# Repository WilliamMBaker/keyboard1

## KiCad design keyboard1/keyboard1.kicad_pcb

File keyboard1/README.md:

This is a Kicad Template project (that also happens to be a dev-board) for the STM32F072CBT6.

***THIS PROJECT IS NOT PIN-COMPATIBLE OR PHYSICALLY COMPATIBLE WITH PROJECTS THAT USE A BLACKPILL OR ANY OTHER STM DEV-BOARD***

**THIS IS NOT A BLACKPILL OR BLUEPILL REPLACEMENT**

****See this video for turning this template into a BlackPill-compatible dev board:**** https://youtu.be/LvX-Us9VZM0

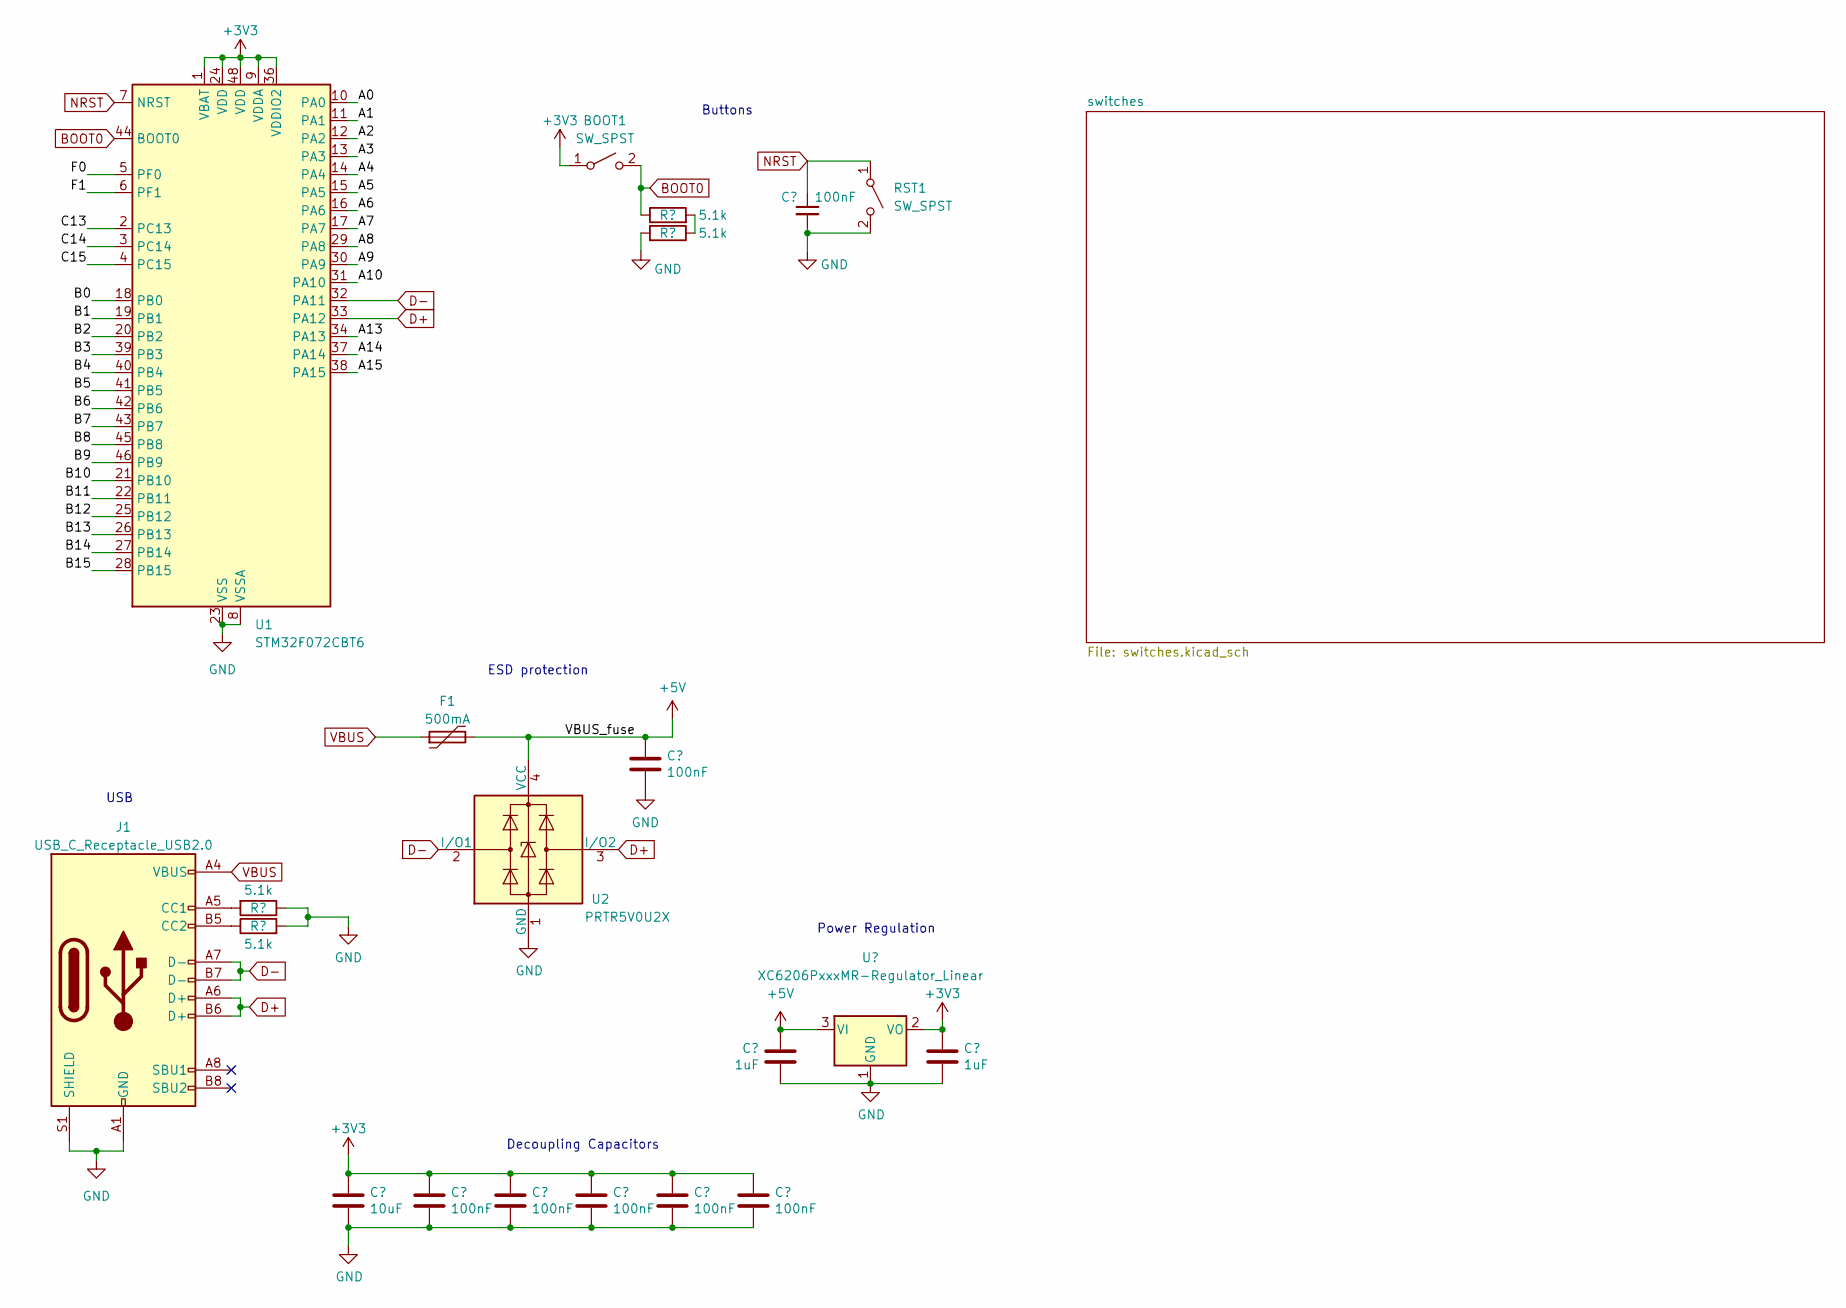
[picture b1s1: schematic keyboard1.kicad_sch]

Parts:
BOOT1: SW_SPST; SW_SPST_TL3342
C1, C3, C4, C5, C6, C7, C8: 100nF; C_0402_1005Metric; LCSC C307331
C2: 10uF; C_0603_1608Metric; LCSC C307331
C9, C10: 1uF; C_0402_1005Metric; LCSC C307331
F1: 500mA; Fuse_1206_3216Metric; LCSC C135341
J1: USB_C_Receptacle_USB2.0; USB_C_Receptacle_HRO_TYPE-C-31-M-12; JlcRotOffset 180
R1, R2, R3, R4: 5.1k; R_0402_1005Metric
RST1: SW_SPST; SW_SPST_TL3342
U1: STM32F072CBT6; LQFP-48_7x7mm_P0.5mm; JlcRotOffset 90
U2: PRTR5V0U2X; SOT-143; LCSC C2827688
U3: XC6206PxxxMR-Regulator_Linear; SOT-23; LCSC C5446

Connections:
+3V3: BOOT1.1 (A), C2.1, C3.1, C4.1, C5.1, C6.1, C7.1, C10.1, U1.1 (VBAT), U1.9 (VDDA), U1.24 (VDD), U1.36 (VDDIO2), U1.48 (VDD), U3.2 (VO)
+5V: C8.1, C9.1, F1.2, U2.4 (VCC), U3.3 (VI)
/A0: U1.10 (PA0)
/A1: U1.11 (PA1)
/A2: U1.12 (PA2)
/A3: U1.13 (PA3)
/A4: U1.14 (PA4)
/A5: U1.15 (PA5)
/A6: U1.16 (PA6)
/A7: U1.17 (PA7)
/A8: U1.29 (PA8)
/A9: U1.30 (PA9)
/A10: U1.31 (PA10)
/A13: U1.34 (PA13)
/A14: U1.37 (PA14)
/A15: U1.38 (PA15)
/B0: U1.18 (PB0)
/B1: U1.19 (PB1)
/B2: U1.20 (PB2)
/B3: U1.39 (PB3)
/B4: U1.40 (PB4)
/B5: U1.41 (PB5)
/B6: U1.42 (PB6)
/B7: U1.43 (PB7)
/B8: U1.45 (PB8)
/B9: U1.46 (PB9)
/B10: U1.21 (PB10)
/B11: U1.22 (PB11)
/B12: U1.25 (PB12)
/B13: U1.26 (PB13)
/B14: U1.27 (PB14)
/B15: U1.28 (PB15)
/C13: U1.2 (PC13)
/C14: U1.3 (PC14)
/C15: U1.4 (PC15)
/F0: U1.5 (PF0)
/F1: U1.6 (PF1)
BOOT0: BOOT1.2 (B), R3.1, U1.44 (BOOT0)
D+: J1.A6 (D+), J1.B6 (D+), U1.33 (PA12), U2.3 (I/O2)
D-: J1.A7 (D-), J1.B7 (D-), U1.32 (PA11), U2.2 (I/O1)
GND: C1.2, C2.2, C3.2, C4.2, C5.2, C6.2, C7.2, C8.2, C9.2, C10.2, J1.A1 (GND), J1.A12 (GND), J1.B1 (GND), J1.B12 (GND), J1.S1 (SHIELD), R1.1, R2.2, R4.2, RST1.2 (B), U1.8 (VSSA), U1.23 (VSS), U1.35 (VSS), U1.47 (VSS), U2.1 (GND), U3.1 (GND)
NRST: C1.1, RST1.1 (A), U1.7 (NRST)
unnamed: J1.A5 (CC1), R1.2
unnamed: J1.B5 (CC2), R2.1
unnamed: R3.2, R4.1
VBUS: F1.1, J1.A4 (VBUS), J1.A9 (VBUS), J1.B4 (VBUS), J1.B9 (VBUS)

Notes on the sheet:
Buttons
Decoupling Capacitors
ESD protection
USB
Power Regulation

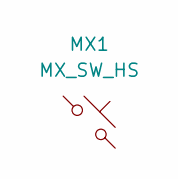
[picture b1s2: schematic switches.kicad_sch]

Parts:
MX1: MX_SW_HS; SW_MX_HS_CPG151101S11_1u

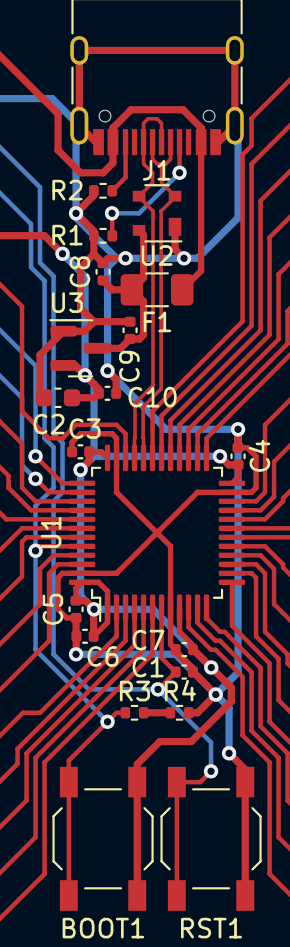
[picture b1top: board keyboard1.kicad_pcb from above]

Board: 2 copper layers, 21 parts (0 on the bottom side), 11 nets.

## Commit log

2024-10-26 Add README
